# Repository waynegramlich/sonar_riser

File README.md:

# sonar_riser
Sonar Riser for HC-SR04

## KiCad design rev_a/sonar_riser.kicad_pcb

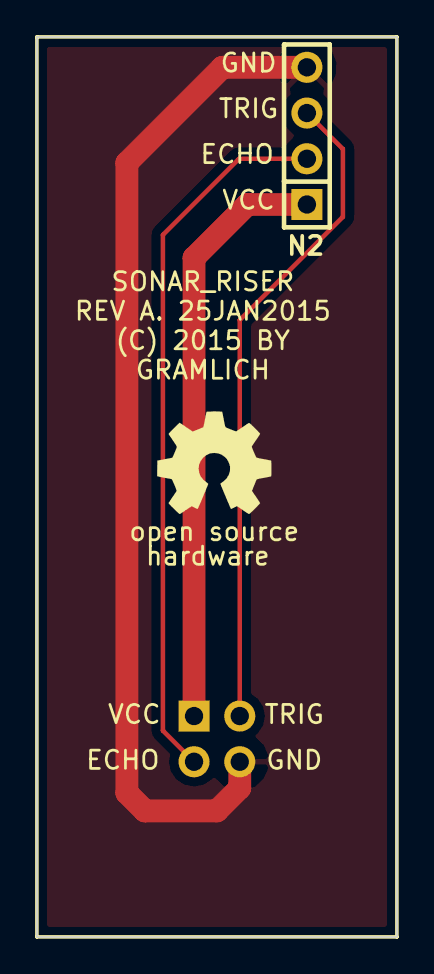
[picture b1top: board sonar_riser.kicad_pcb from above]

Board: 2 copper layers, 20.0 x 50.0 mm, 3 parts (1 on the bottom side), 4 nets.

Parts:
N1: SONAR_MASTER; Pin_Header_Straight_2x02
N2: SONAR_SLAVE; Pin_Header_Straight_1x04
OSHW1: OSHW; OSHW_LOGO_250mil

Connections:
/GND: N1.4, N2.4
/VCC: N1.1, N2.1
unnamed: N1.2, N2.2
unnamed: N1.3, N2.3

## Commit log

2015-01-26 Got Rev. A layed out.
2015-01-27 Checked off [] Protel gerber suffixes.

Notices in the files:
rev_a/sonar_riser.kicad_pcb:
(C) 2015 BY
GRAMLICH
